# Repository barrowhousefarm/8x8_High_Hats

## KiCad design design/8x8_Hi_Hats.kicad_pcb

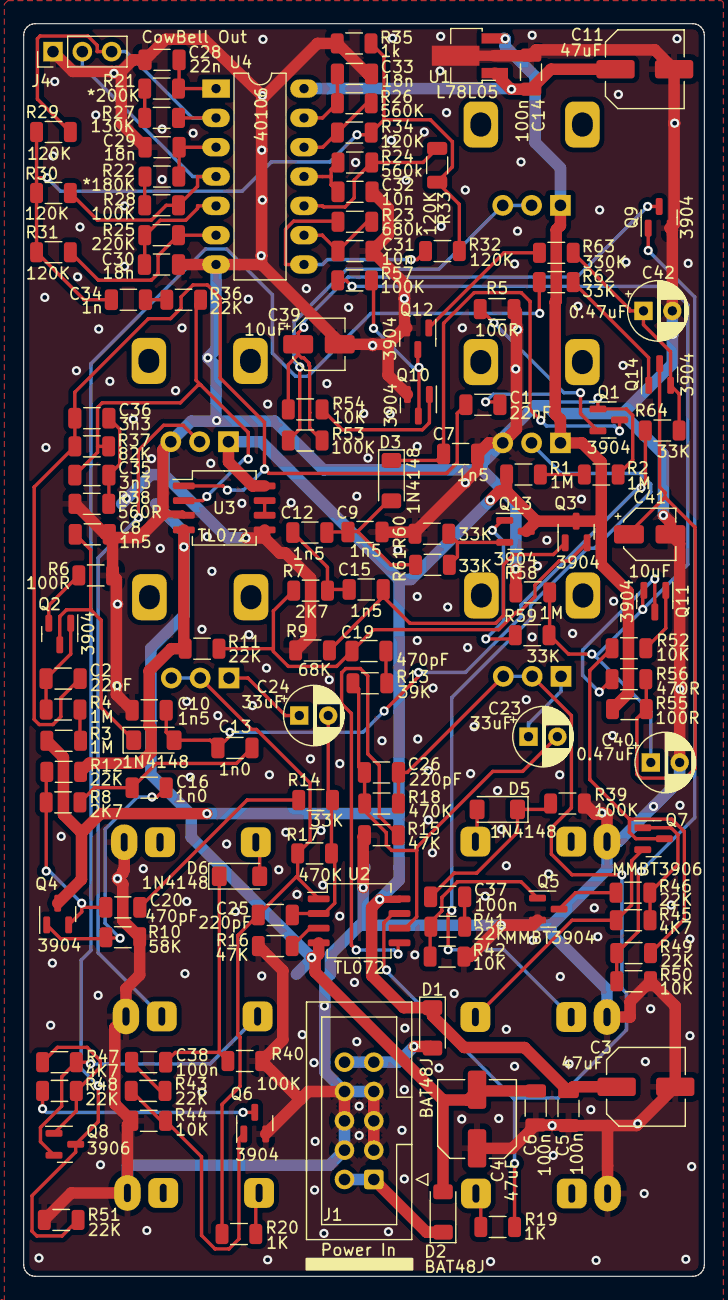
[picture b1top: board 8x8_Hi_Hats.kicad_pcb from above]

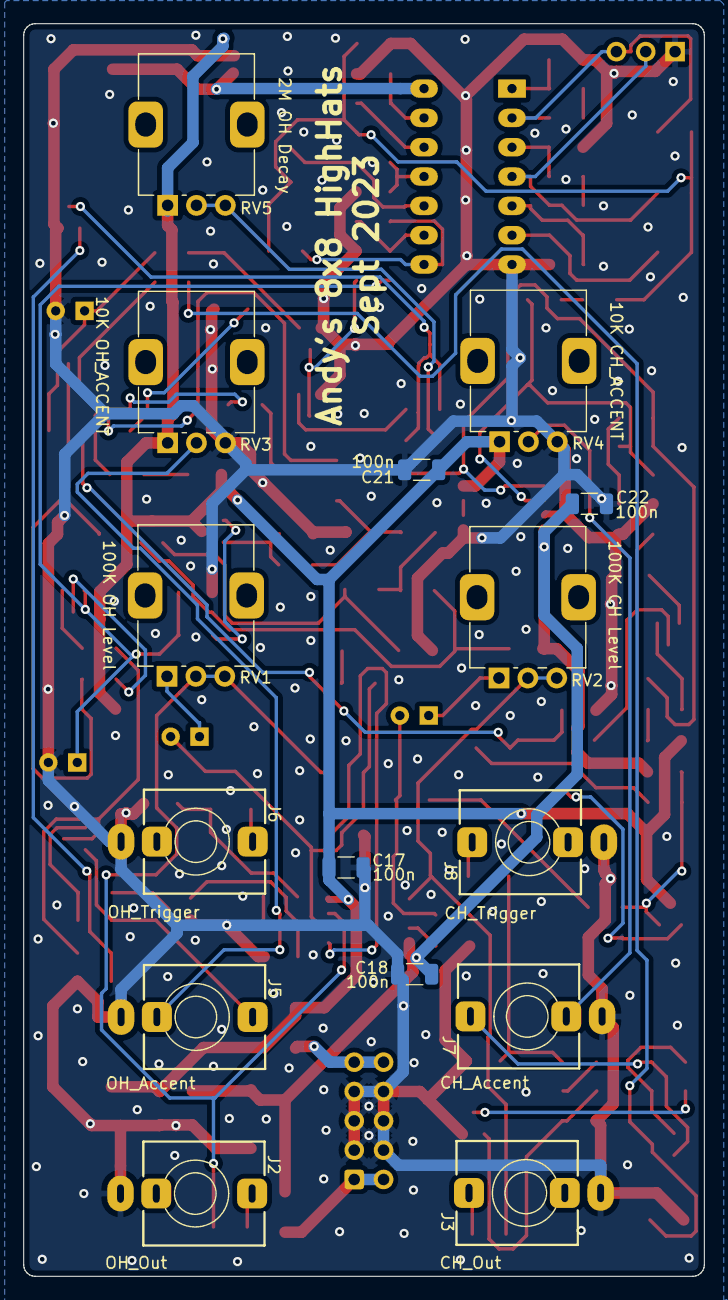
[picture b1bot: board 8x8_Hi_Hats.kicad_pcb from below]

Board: 2 copper layers, 59.0 x 108.5 mm, 142 parts (15 on the bottom side), 86 nets.

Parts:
C1, C2: 22nF; C_1206_3216Metric
C3, C4, C11: 47uF; C_Elec_6.3x5.4
C5, C6, C14, C17, C18, C21, C22, C37, C38: 100n; C_1206_3216Metric
C7, C8, C9, C10, C12, C15: 1n5; C_1206_3216Metric
C13, C16: 1n0; C_1206_3216Metric
C19, C20: 470pF; C_1206_3216Metric
C23, C24: 33uF; CP_Radial_D5.0mm_P2.50mm
C25, C26: 220pF; C_1206_3216Metric
C28: 22n; C_1206_3216Metric
C29, C30, C33: 18n; C_1206_3216Metric
C31, C32: 10n; C_1206_3216Metric
C34: 1n; C_1206_3216Metric
C35, C36: 3n3; C_1206_3216Metric
C39, C41: 10uF; CP_Elec_4x5.4
C40, C42: 0.47uF; CP_Radial_D5.0mm_P2.50mm
D1, D2: BAT48J; D_MiniMELF
D3, D4, D5, D6: 1N4148; D_MiniMELF
J1: Power In; IDC-Header_2x05_P2.54mm_Vertical
J2: OH_Out; Jack_3.5mm_QingPu_WQP-PJ398SM_Vertical
J3: CH_Out; Jack_3.5mm_QingPu_WQP-PJ398SM_Vertical
J4: CowBell Out; PinHeader_1x03_P2.54mm_Vertical
J5: OH_Accent; Jack_3.5mm_QingPu_WQP-PJ398SM_Vertical
J6: OH_Trigger; Jack_3.5mm_QingPu_WQP-PJ398SM_Vertical
J7: CH_Accent; Jack_3.5mm_QingPu_WQP-PJ398SM_Vertical
J8: CH_Trigger; Jack_3.5mm_QingPu_WQP-PJ398SM_Vertical
Q1, Q2, Q3, Q4, Q6, Q9, Q10, Q11, Q12, Q13, Q14: 3904; SOT-23
Q5: MMBT3904; SOT-23
Q7: MMBT3906; SOT-23
Q8: 3906; SOT-23
R1, R2, R3, R4, R58: 1M; R_1206_3216Metric
R5, R6, R55: 100R; R_1206_3216Metric
R7, R8: 2K7; R_1206_3216Metric
R9: 68K; R_1206_3216Metric
R10: 58K; R_1206_3216Metric
R11, R12, R36, R41, R43, R46, R48, R49, R51: 22K; R_1206_3216Metric
R13: 39K; R_1206_3216Metric
R14, R59, R60, R61, R62, R64: 33K; R_1206_3216Metric
R15, R16: 47K; R_1206_3216Metric
R17, R18: 470K; R_1206_3216Metric
R19, R20: 1K; R_1206_3216Metric
R21: *200K; R_1206_3216Metric
R22: *180K; R_1206_3216Metric
R23: 680k; R_1206_3216Metric
R24: 560k; R_1206_3216Metric
R25: 220K; R_1206_3216Metric
R26: 560K; R_1206_3216Metric
R27: 130K; R_1206_3216Metric
R28, R39, R40, R53, R57: 100K; R_1206_3216Metric
R29, R30, R31, R32, R33, R34: 120K; R_1206_3216Metric
R35: 1k; R_1206_3216Metric
R37: 82K; R_1206_3216Metric
R38: 560R; R_1206_3216Metric
R42, R44, R50, R52, R54: 10K; R_1206_3216Metric
R45, R47: 4K7; R_1206_3216Metric
R56: 470R; R_1206_3216Metric
R63: 330K; R_1206_3216Metric
RV1: 100K OH Level; Potentiometer_Alps_RK09K_Single_Vertical
RV2: 100K CH Level; Potentiometer_Alps_RK09K_Single_Vertical
RV3: 10K OH_ACCENT; Potentiometer_Alps_RK09K_Single_Vertical
RV4: 10K CH_ACCENT; Potentiometer_Alps_RK09K_Single_Vertical
RV5: 2M OH Decay; Potentiometer_Alps_RK09K_Single_Vertical
U1: L78L05; SOT-89-3_Handsoldering
U2, U3: TL072; SO-8_5.3x6.2mm_P1.27mm
U4: 40106; DIP-14_W7.62mm_LongPads

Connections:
+5V: C11.1, C14.1, U1.1 (VO), U4.14 (VDD)
+12V: C3.1, C5.1, C17.1, C21.1, D1.1 (K), Q3.3 (C), Q4.3 (C), Q13.3 (C), R1.1, R3.1, R55.2, RV3.1, RV4.1, RV5.1, U1.3 (VI), U2.8 (V+), U3.8 (V+)
-12V: C4.2, C6.2, C18.2, C22.2, D2.2 (A), R11.2, R12.2, U2.4 (V-), U3.4 (V-)
/Trigger_choke/CH_Accent: J7.T, Q8.2 (E), R47.2
/Trigger_choke/OH_Accent: J5.T, Q7.2 (E), R45.2
CH_Fire: C10.2, C13.1, D4.2 (A), R64.1
CH_Out: J3.T, R20.2
CH_Trigger: Q8.3 (C), R51.2, R62.1
GND: C3.2, C4.1, C5.2, C6.1, C7.1, C8.1, C9.1, C10.1, C11.2, C14.2, C17.2, C18.1, C21.2, C22.1, C28.1, C29.1, C30.1, C31.1, C32.1, C33.1, C39.2, C40.2, C41.2, C42.2, J1.3, J1.4, J1.5, J1.6, J1.7, J1.8, J2.S, J3.S, J4.1, J5.S, J6.S, J7.S, J8.S, Q5.2 (E), Q6.2 (E), Q9.2 (E), Q10.2 (E), Q12.2 (E), R5.2, R6.2, R9.2, R10.2, R15.1, R16.1, R35.1, R38.1, R39.1, R40.1, R42.1, R44.1, R50.2, R51.1, R58.1, R60.1, RV3.3, RV4.3, U1.2 (GND), U3.3 (+), U3.5 (+), U4.7 (VSS)
unnamed: C12.2, C15.1, R7.1
unnamed: C13.2, C16.1, R8.1
unnamed: C19.2, R13.1
unnamed: C20.2, R14.1
unnamed: C23.1, RV1.1
unnamed: C24.1, RV2.1
unnamed: C25.2, R17.2, R20.1, RV2.2, RV2.3, U2.1
unnamed: C26.2, R18.2, R19.1, RV1.2, RV1.3, U2.7
unnamed: C28.2, R21.1, U4.1
unnamed: C29.2, R22.1, U4.3
unnamed: C30.2, R25.1, U4.5
unnamed: C31.2, R23.1, U4.9
unnamed: C32.2, R24.1, U4.11
unnamed: C33.2, R26.1, U4.13
unnamed: C34.1, R29.2, R30.2, R31.2, R32.2, R33.2, R34.2, R35.2
unnamed: C34.2, R36.1
unnamed: C35.2, C36.1, R38.2
unnamed: C37.2, R41.2
unnamed: C38.2, R43.2
unnamed: D1.2 (A), J1.9, J1.10
unnamed: D2.1 (K), J1.1, J1.2
unnamed: C7.2, D3.1 (K), Q1.3 (C)
unnamed: C8.2, D4.1 (K), Q2.3 (C)
unnamed: D5.2 (A), J6.T
unnamed: C37.1, D5.1 (K), R39.2
unnamed: D6.2 (A), J8.T
unnamed: C38.1, D6.1 (K), R40.2
unnamed: J4.2, R28.2, R30.1, U4.4
unnamed: J4.3, R27.2, R29.1, U4.2
unnamed: J5.TN, RV3.2
unnamed: J7.TN, RV4.2
unnamed: C1.2, Q1.1 (B), R2.2
unnamed: Q1.2 (E), R5.1
unnamed: C2.2, Q2.1 (B), R4.2
unnamed: Q2.2 (E), R6.1
unnamed: C15.2, Q3.1 (B), R9.1
unnamed: C19.1, Q3.2 (E), R7.2, R11.1
unnamed: C16.2, Q4.1 (B), R10.1
unnamed: C20.1, Q4.2 (E), R8.2, R12.1
unnamed: Q5.1 (B), R41.1, R42.2
unnamed: Q5.3 (C), R46.1
unnamed: Q6.1 (B), R43.1, R44.2
unnamed: Q6.3 (C), R48.1
unnamed: Q7.1 (B), R45.1, R46.2
unnamed: Q8.1 (B), R47.1, R48.2
unnamed: C39.1, Q9.3 (C), R53.1, R54.2
unnamed: Q10.1 (B), R54.1
unnamed: Q10.3 (C), Q12.3 (C), R57.1
unnamed: Q11.1 (B), R52.2
unnamed: Q11.3 (C), R56.1
unnamed: C40.1, Q11.2 (E), R57.2, R58.2, R59.2
unnamed: Q12.1 (B), R63.1
unnamed: Q13.1 (B), R59.1
unnamed: Q13.2 (E), R60.2, R61.2
unnamed: Q14.1 (B), R62.2
unnamed: C41.1, Q14.3 (C), R55.1, R56.2
unnamed: C42.1, Q14.2 (E), R63.2, R64.2
unnamed: R1.2, R2.1
unnamed: R3.2, R4.1
unnamed: R21.2, R27.1
unnamed: R22.2, R28.1
unnamed: R23.2, R32.1, U4.8
unnamed: R24.2, R33.1, U4.10
unnamed: R25.2, R31.1, U4.6
unnamed: R26.2, R34.1, U4.12
unnamed: R53.2, RV5.2, RV5.3
unnamed: R16.2, U2.3 (+)
unnamed: C24.2, C25.1, R14.2, R17.1, U2.2 (-)
unnamed: R15.2, U2.5 (+)
unnamed: C23.2, C26.1, R13.2, R18.1, U2.6 (-)
unnamed: C35.1, R36.2, R37.1, U3.2 (-)
unnamed: U3.6 (-), U3.7
Noise: C1.1, C2.1, C36.2, R37.2, U3.1
OH_Fire: C9.2, C12.1, D3.2 (A), R61.1
OH_Out: J2.T, R19.2
OH_Trig_Choke: Q9.1 (B), R49.1, R50.1
OH_Trigger: Q7.3 (C), R49.2, R52.1
